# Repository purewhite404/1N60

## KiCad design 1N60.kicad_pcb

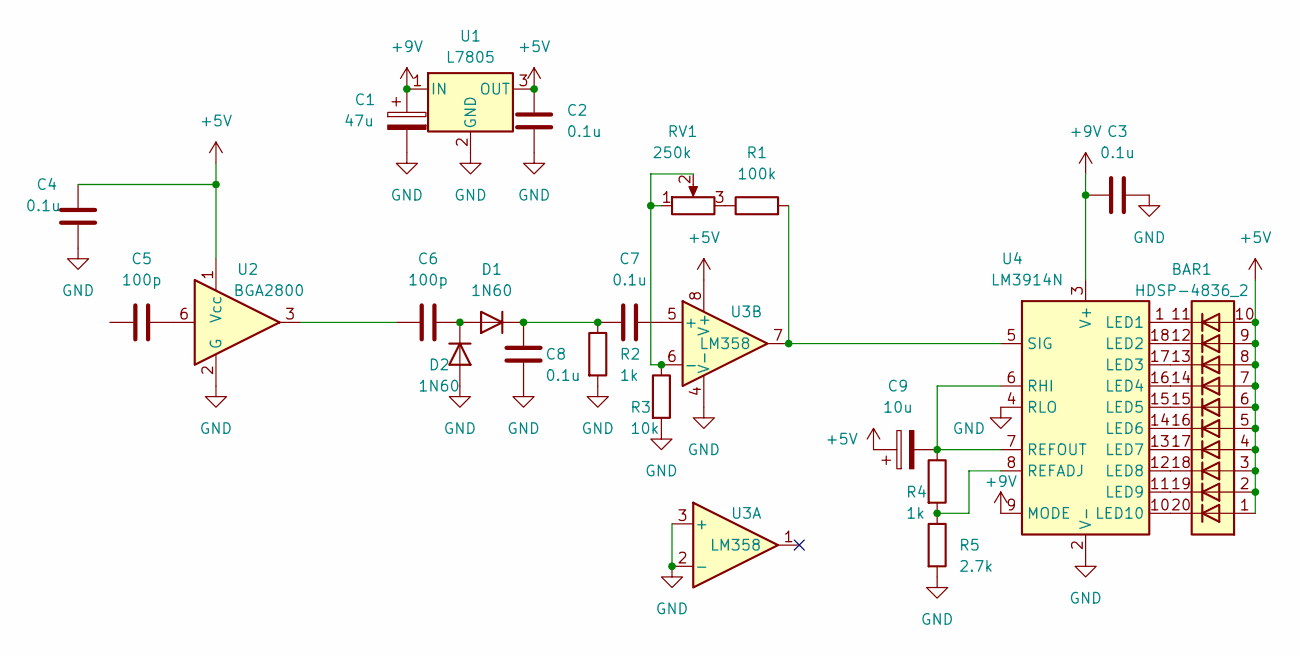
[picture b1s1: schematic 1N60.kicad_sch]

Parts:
BAR1: HDSP-4836_2; HDSP-4836
C1: 47u; CP_Radial_D6.3mm_P2.50mm
C2, C3, C4, C7, C8: 0.1u; C_Disc_D4.3mm_W1.9mm_P5.00mm
C5, C6: 100p; C_Disc_D4.3mm_W1.9mm_P5.00mm
C9: 10u; CP_Radial_D6.3mm_P2.50mm
D1, D2: 1N60; D_A-405_P7.62mm_Horizontal
R1: 100k; R_Axial_DIN0207_L6.3mm_D2.5mm_P7.62mm_Horizontal
R2, R4: 1k; R_Axial_DIN0207_L6.3mm_D2.5mm_P7.62mm_Horizontal
R3: 10k; R_Axial_DIN0207_L6.3mm_D2.5mm_P7.62mm_Horizontal
R5: 2.7k; R_Axial_DIN0207_L6.3mm_D2.5mm_P7.62mm_Horizontal
RV1: 250k; PinHeader_1x03_P2.54mm_Vertical
U1: L7805; TO-220-3_Vertical
U2: BGA2800; DIP-6_W7.62mm
U3: LM358; DIP-8_W7.62mm
U4: LM3914N; DIP-18_W7.62mm

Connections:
+5V: BAR1.1 (A), BAR1.2 (A), BAR1.3 (A), BAR1.4 (A), BAR1.5 (A), BAR1.6 (A), BAR1.7 (A), BAR1.8 (A), BAR1.9 (A), BAR1.10 (A), C2.1, C4.1, C9.1, U1.3 (OUT), U2.1 (Vcc), U3.8 (V+)
+9V: C1.1, C3.1, U1.1 (IN), U4.3 (V+), U4.9 (MODE)
GND: C1.2, C2.2, C3.2, C4.2, C8.2, D2.2 (A), R2.2, R3.2, R5.2, U1.2 (GND), U2.2 (G), U2.4 (G), U2.5 (G), U3.2 (-), U3.3 (+), U3.4 (V-), U4.2 (V-), U4.4 (RLO)
unnamed: C5.2, U2.6
unnamed: C6.1, U2.3
unnamed: C6.2, D1.2 (A), D2.1 (K)
unnamed: C7.1, C8.1, D1.1 (K), R2.1
unnamed: R1.1, RV1.3
unnamed: C7.2, U3.5 (+)
unnamed: R3.1, RV1.1, RV1.2, U3.6 (-)
unnamed: BAR1.11 (K), U4.1 (LED1)
unnamed: BAR1.12 (K), U4.18 (LED2)
unnamed: BAR1.13 (K), U4.17 (LED3)
unnamed: BAR1.14 (K), U4.16 (LED4)
unnamed: BAR1.15 (K), U4.15 (LED5)
unnamed: BAR1.16 (K), U4.14 (LED6)
unnamed: BAR1.17 (K), U4.13 (LED7)
unnamed: BAR1.18 (K), U4.12 (LED8)
unnamed: BAR1.19 (K), U4.11 (LED9)
unnamed: BAR1.20 (K), U4.10 (LED10)
unnamed: R4.2, R5.1, U4.8 (REFADJ)
unnamed: C9.2, R4.1, U4.6 (RHI), U4.7 (REFOUT)
unnamed: R1.2, U3.7, U4.5 (SIG)

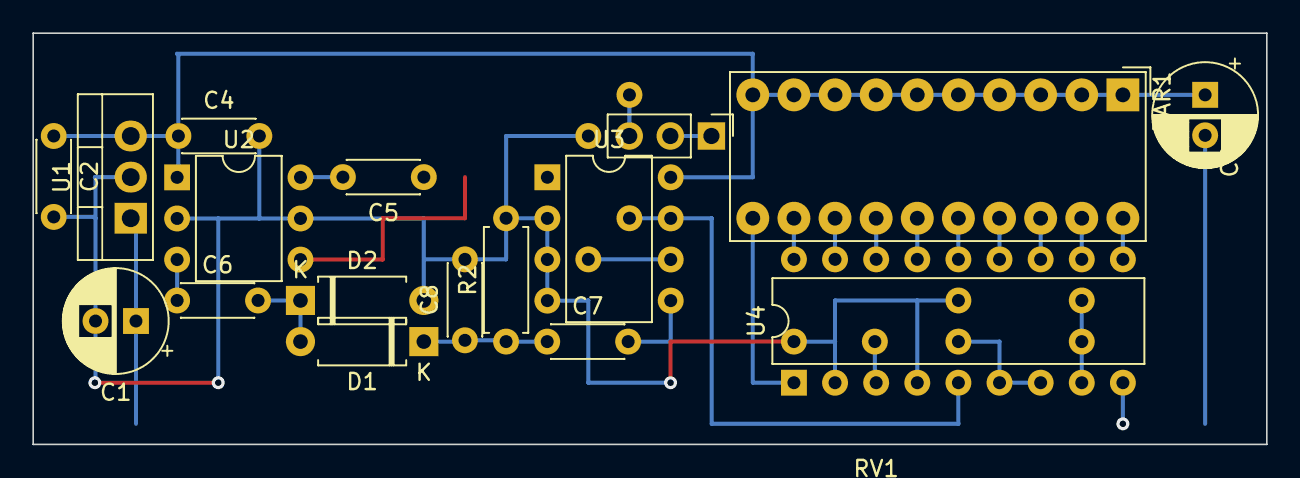
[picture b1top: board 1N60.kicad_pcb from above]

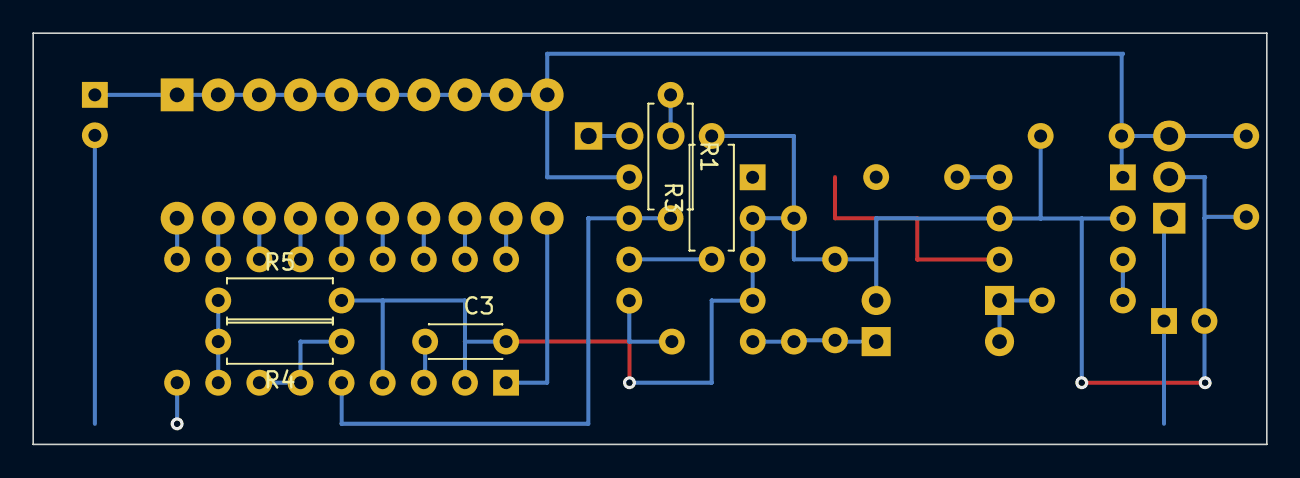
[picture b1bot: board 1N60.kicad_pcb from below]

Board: 2 copper layers, 76.2 x 25.4 mm, 22 parts (5 on the bottom side), 23 nets.

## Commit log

2024-03-18 init
